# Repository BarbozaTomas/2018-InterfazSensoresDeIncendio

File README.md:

# 2018-InterfazSensoresDeIncendio
Interfaz para conectar sensores de incendio comerciales a la central desarrollada

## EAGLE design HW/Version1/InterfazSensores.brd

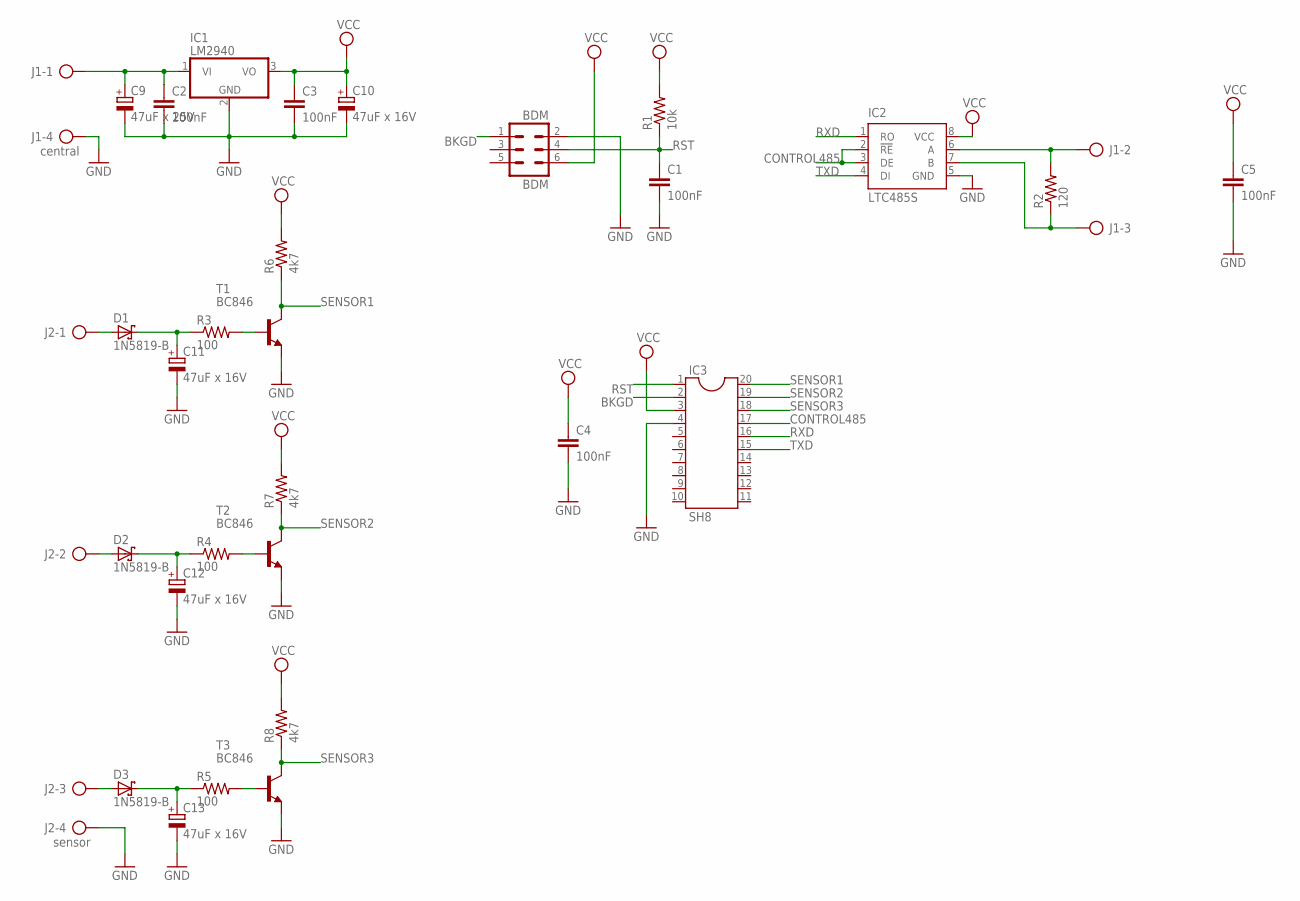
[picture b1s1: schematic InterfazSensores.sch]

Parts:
BDM: BDM; MA03-2
C1, C2, C3, C4, C5: 100nF; C0805
C9: 47uF x 25V; E2,5-6E
C10, C11, C12, C13: 47uF x 16V; E2,5-6E
D1, D2, D3: 1N5819-B; DO41-7.6
IC1: LM2940; TO220V
IC2: LTC485S; SOIC8
IC3: SH8; DIL20
J1: central; AK300/4
J2: sensor; AK300/4
R1: 10k; R0805
R2: 120; R0805
R3, R4, R5: 100; R0805
R6, R7, R8: 4k7; R0805
T1, T2, T3: BC846; SOT23

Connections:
BKGD: BDM.1, IC3.2
CONTROL485: IC2.2 (!RE), IC2.3 (DE), IC3.17
GND: BDM.2, C1.2, C2.2, C3.2, C4.2, C5.2, C9.-, C10.-, C11.-, C12.-, C13.-, IC1.2 (GND), IC2.5 (GND), IC3.4, J1.4, J2.4, T1.2 (E), T2.2 (E), T3.2 (E)
unnamed: C2.1, C9.+, IC1.1 (VI), J1.1
unnamed: IC2.6 (A), J1.2, R2.2
unnamed: IC2.7 (B), J1.3, R2.1
unnamed: D1.A, J2.1
unnamed: D2.A, J2.2
unnamed: D3.A, J2.3
unnamed: C11.+, D1.C, R3.1
unnamed: C12.+, D2.C, R4.1
unnamed: C13.+, D3.C, R5.1
unnamed: R5.2, T3.1 (B)
unnamed: R4.2, T2.1 (B)
unnamed: R3.2, T1.1 (B)
RST: BDM.4, C1.1, IC3.1, R1.1
RXD: IC2.1 (RO), IC3.16
SENSOR1: IC3.20, R6.1, T1.3 (C)
SENSOR2: IC3.19, R7.1, T2.3 (C)
SENSOR3: IC3.18, R8.1, T3.3 (C)
TXD: IC2.4 (DI), IC3.15
VCC: BDM.6, C3.1, C4.1, C5.1, C10.+, IC1.3 (VO), IC2.8 (VCC), IC3.3, R1.2, R6.2, R7.2, R8.2

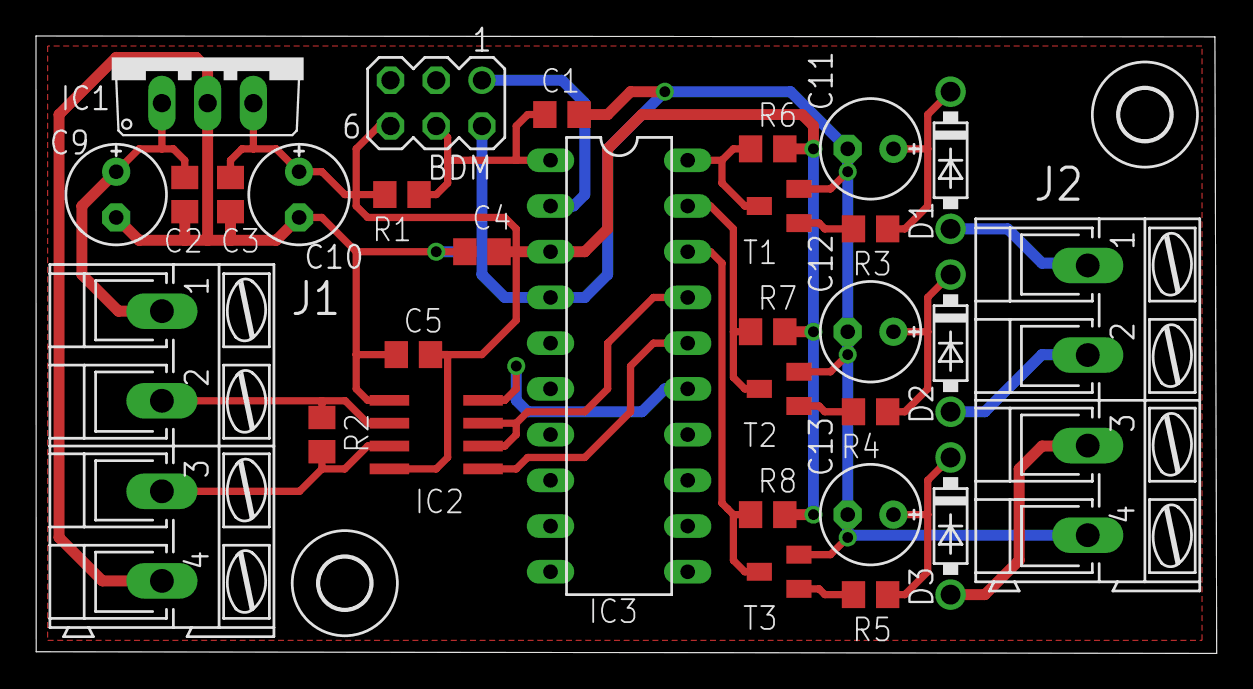
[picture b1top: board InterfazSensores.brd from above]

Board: 2 copper layers, 65.6 x 34.3 mm, 32 parts (0 on the bottom side), 22 nets.

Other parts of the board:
U$1, U$3: 2,8

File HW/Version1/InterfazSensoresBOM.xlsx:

BOM Interfaz Sensores |  |  |  | Código ELEMON
Cant. | Description | Value | Precio
1 | Tira de pines macho | Tira 2x40
5 | Cap. Cerámico SMD0805 | 100nF | US$0,01951 | CA3279774
1 | Cap. Electrolítico | 47uF x 25V | US$0,13124 | CA3629260
4 | Cap. Electrolítico | 47uF x 16V | US$0,14280 | CA3629110
3 | Diodo SCHOTTKY | 1N5819 | US$0,6583 | DI1351301
1 | Regulador de voltaje descriptivo | LM2940
1 | Transmisor de interfaz de baja potencia | LTC485S
1 | Microcontrolador 8bits | MC9S08SH8
2 | Bornera cuadruple AK300/4
1 | Resistencia SMD0805 | 10k | US$0,00477 | RS3896245
1 | Resistencia SMD0805 | 120 | US$0,00476 | RS3896129
3 | Resistencia SMD0805 | 100 | US$0,00471 | RS3896126
3 | Resistencia SMD0805 | 4,7k | US$0,00476 | RS3896224
3 | NPN Transistor SOT23 | BC846 | US$0,04001 | TR1723040

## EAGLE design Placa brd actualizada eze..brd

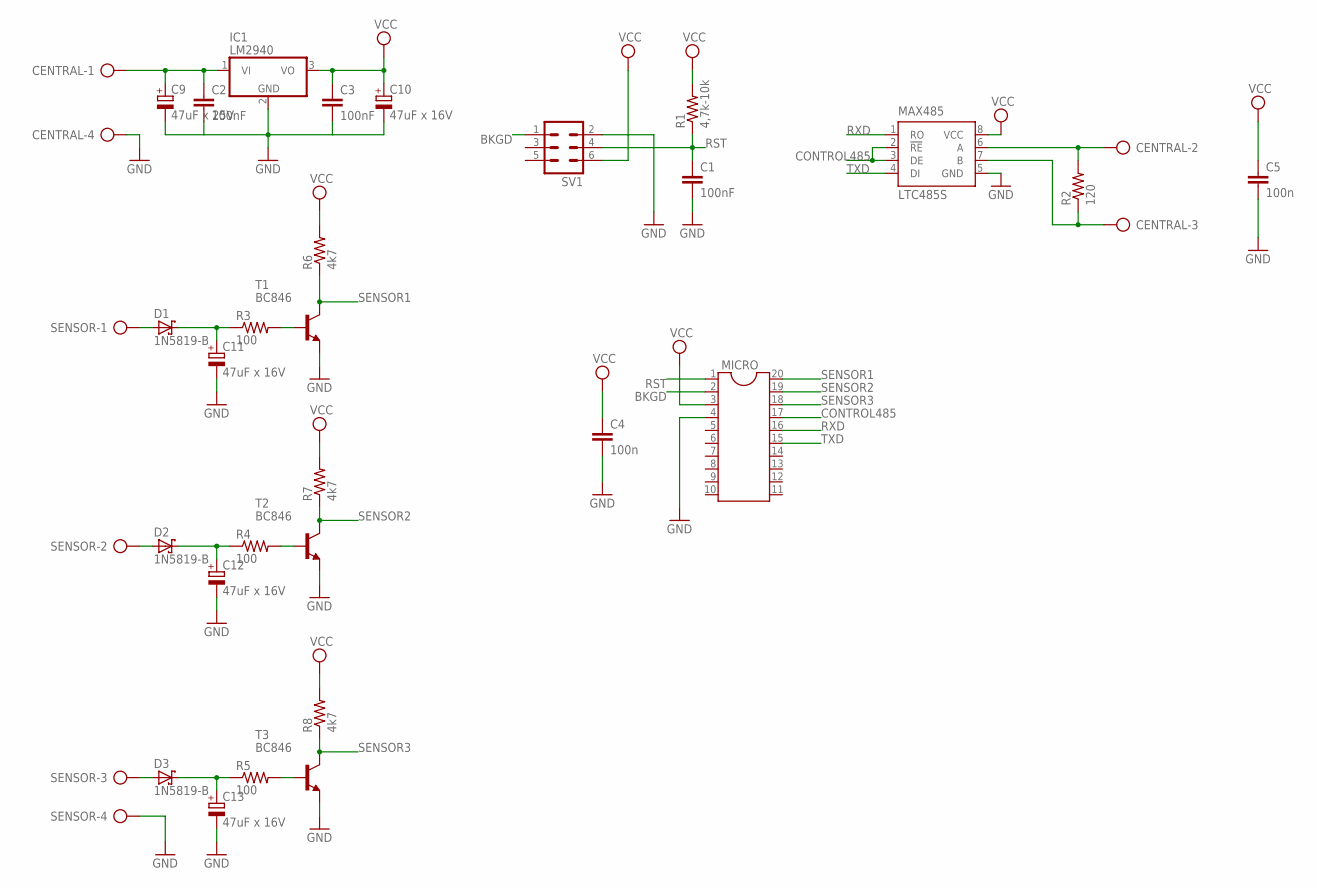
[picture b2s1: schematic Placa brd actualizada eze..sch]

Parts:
C1, C2, C3: 100nF; C0805
C4, C5: 100n; C0805
C9: 47uF x 25V; E2,5-6E
C10, C11, C12, C13: 47uF x 16V; E2,5-6E
CENTRAL: AK300/4
D1, D2, D3: 1N5819-B; DO41-7.6
IC1: LM2940; TO220V
MAX485: LTC485S; SOIC8
MICRO: DIL20
R1: 4,7k-10k; R0805
R2: 120; R0805
R3, R4, R5: 100; R0805
R6, R7, R8: 4k7; R0805
SENSOR: AK300/4
SV1: MA03-2
T1, T2, T3: BC846; SOT23

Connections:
BKGD: MICRO.2, SV1.1
CONTROL485: MAX485.2 (!RE), MAX485.3 (DE), MICRO.17
GND: C1.2, C2.2, C3.2, C4.2, C5.2, C9.-, C10.-, C11.-, C12.-, C13.-, CENTRAL.4, IC1.2 (GND), MAX485.5 (GND), MICRO.4, SENSOR.4, SV1.2, T1.2 (E), T2.2 (E), T3.2 (E)
unnamed: C2.1, C9.+, CENTRAL.1, IC1.1 (VI)
unnamed: CENTRAL.2, MAX485.6 (A), R2.2
unnamed: CENTRAL.3, MAX485.7 (B), R2.1
unnamed: D1.A, SENSOR.1
unnamed: D2.A, SENSOR.2
unnamed: D3.A, SENSOR.3
unnamed: C11.+, D1.C, R3.1
unnamed: C12.+, D2.C, R4.1
unnamed: C13.+, D3.C, R5.1
unnamed: R5.2, T3.1 (B)
unnamed: R4.2, T2.1 (B)
unnamed: R3.2, T1.1 (B)
RST: C1.1, MICRO.1, R1.1, SV1.4
RXD: MAX485.1 (RO), MICRO.16
SENSOR1: MICRO.20, R6.1, T1.3 (C)
SENSOR2: MICRO.19, R7.1, T2.3 (C)
SENSOR3: MICRO.18, R8.1, T3.3 (C)
TXD: MAX485.4 (DI), MICRO.15
VCC: C3.1, C4.1, C5.1, C10.+, IC1.3 (VO), MAX485.8 (VCC), MICRO.3, R1.2, R6.2, R7.2, R8.2, SV1.6

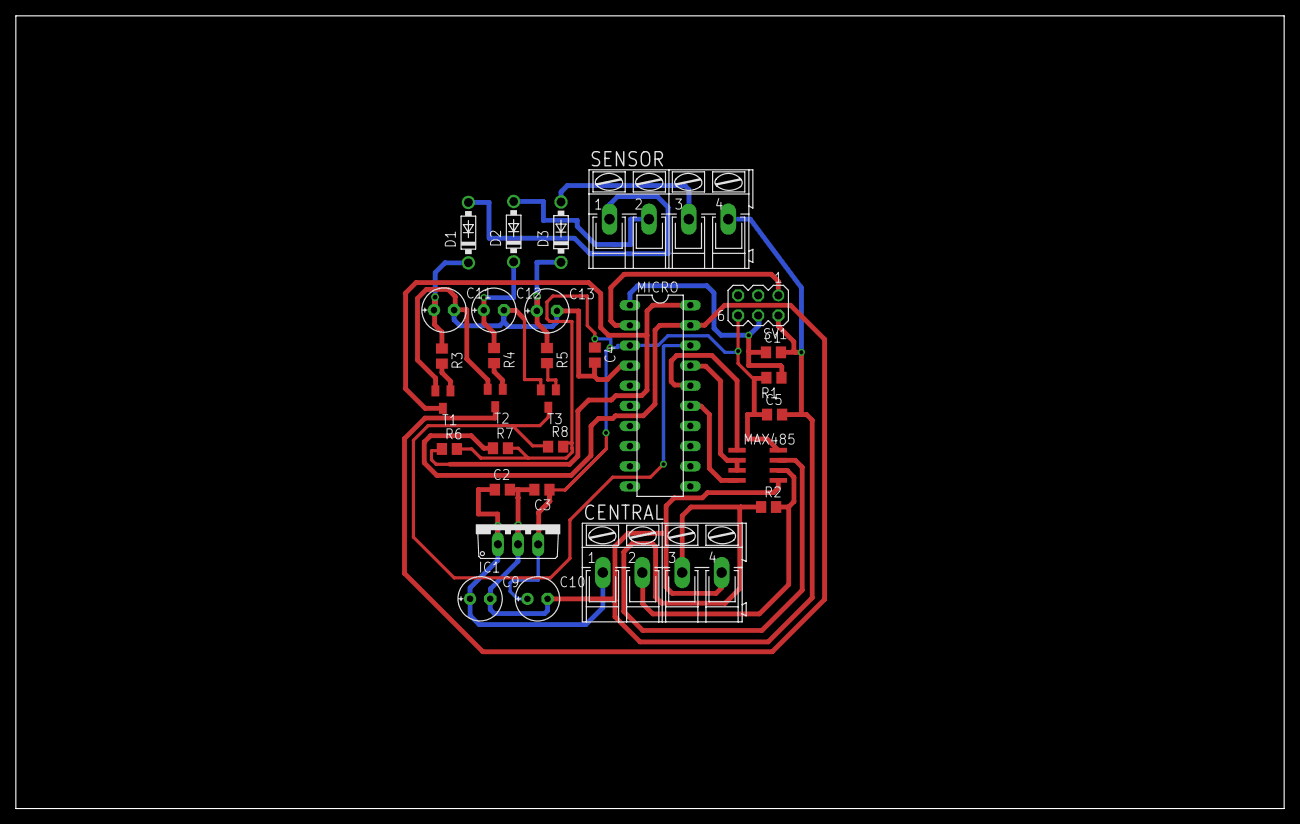
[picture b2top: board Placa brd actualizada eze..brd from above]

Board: 2 copper layers, 160.0 x 100.0 mm, 30 parts (0 on the bottom side), 22 nets.

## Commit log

2018-04-12 Create ToDo
2018-04-13 Archivo ToDo - Carpeta SW
    Cambio extensión de ToDo a txt y agrego carpeta SW y ToDo.txt
    correspondiente.
2018-04-13 Subi archivos
    Subi archivo de ERS y archivo del Gantt
2018-04-16 Documentos Archivados
    Cree esta carpeta para archivar informacion
2018-04-16 Datasheet
    Datasheets del inegrado max485
2018-04-19 Acomodando
    Agrego carpeta dentro de DOCS para documentos administrativos. Paso ahí el RS y Gantt.
2018-04-23 Datasheet
    Agrego el datasheet del micro sh8
2018-04-23 Datasheet
    Agrego el datasheet del lm2940
2018-04-24 Analisis de mercado
    Aca subimos la carpeta relacionada a la investigacion del mercado
2018-04-24 Investigacion de Mercado
    Aca subimos el archivo de Investigacion de mercado
2018-05-15 Proyecto Eagle
    Agrego el .epf y el .sch de la plaqueta, quedan algunas cosas por terminar en el .sch
2018-05-17 Proyecto Eagle
    Subo el esquematico con los cambios realizados el 17/05/2018
2018-05-17 Proyect Board
    Aca subo lo que hice hasta ahora del board
2018-05-21 Correcciones SCH
    Algunas correcciones, falta revisión final.
2018-05-21 Proyect Board
2018-05-24 Proyecto Eagle
    Esquematico terminado
    Board falta corregir errores
2018-05-24 Brd
    Aca dejo lo que actualize del brd
2018-05-28 Board
    Subo las correcciones que hice en el board.
2018-05-28 Board changes
    Aca subo los cambios que hice en el board.
2018-05-28 Board changes
    Aca subo los cambios que hice en el board
2018-06-04 Acomodo HW
    Renombra archivos y elimina duplicados
2018-06-04 Correcciones
    Corregimos en placa algunas inconsistencias
2018-06-04 Redistribucion
    Cambio layout del PCB, para rutear
2018-06-11 Cambios efectuados en el board
    Cambios que hice en el brd por un problema de grilla.
2018-06-18 Cambios realizados en el board
    Placa board actualizada
2018-06-19 Acomodando repositorio
    Agrupo hojas de datos, paso proyecto de HW a carpeta Version1. Resta revisión final.
2018-06-28 Placa finalizada
    Revisada, lista para fabricar.
2018-06-28 Generado CAM
    Seteado las tareas para GERBER
2018-06-28 Actualizo y agrego lista de materiales
    Lista de materiales actualizada a travez del SCH
2018-07-05 Lista de materiales efectuada
    Acomodamos en Excel la BOM con un presupuesto estimado de los componentes
2018-08-02 Gerbers
    Agrego archivo CAM y Gerbers de la placa
2018-08-27 Ajustes
    Ajustes menores en archivos gerbers
2018-08-27 Create Drivers
